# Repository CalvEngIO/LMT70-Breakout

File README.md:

# LMT70-Breakout
Breakout board for the LMT70/A CMOS analog temperature sensor from Texas Instruments

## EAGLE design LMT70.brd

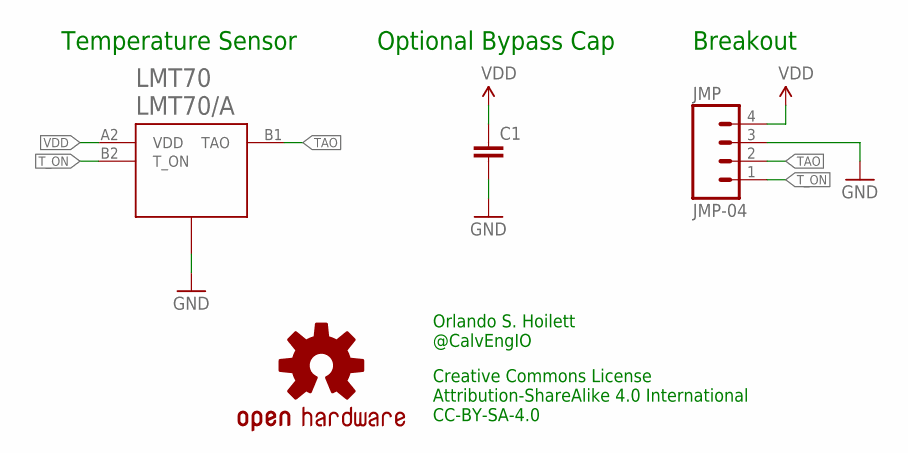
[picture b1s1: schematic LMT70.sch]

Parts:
C1: C-EUC0402; C0402
JMP: JMP-04
LMT70: LMT70/A; 4-DSBGA
LOGO1: OSHW-LOGOM; OSHW-LOGO-M

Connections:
GND: C1.2, JMP.3, LMT70.A1 (GND)
TAO: JMP.2, LMT70.B1 (TAO)
T_ON: JMP.1, LMT70.B2 (T_ON)
VDD: C1.1, JMP.4, LMT70.A2 (VDD)

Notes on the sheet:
Orlando S. Hoilett @CalvEngIO
Creative Commons License Attribution-ShareAlike 4.0 International CC-BY-SA-4.0
Temperature Sensor
Optional Bypass Cap
Breakout

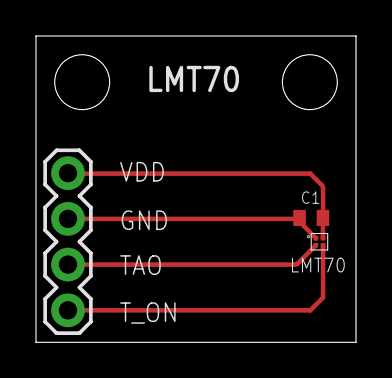
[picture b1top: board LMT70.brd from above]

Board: 2 copper layers, 17.8 x 17.0 mm, 4 parts (1 on the bottom side), 4 nets.

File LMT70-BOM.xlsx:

LMT70 Breakout |  |  |  |  |  |  |  |  |  |  | Total | 4.58
BOM # | Comment | Designator | Description | Mounting Type | Package | Manufacturer | Manufacturer Part Number | Supplier | Supplier Part Number | Quantity | Price per unit | Price Total
1 | LMT70A | LMT70 | Temperature Sensor Analog, Local -55°C ~ 150°C 5.194mV/°C 4-DSBGA (0.9x0.9) | SMD | 4-DSBGA (0.9x0.9) | Texas Insruments | LMT70AYFQT | Digi-Key | 296-42087-1-ND | 1 | 3.74 | 3.74
2 | 40 Pos Male Header Pins | JMP | 40 Positions Header, Breakaway Connector 0.100" (2.54mm) Through Hole Gold | THT | THT | Sullins Connector Solutions | PRPC040SAAN-RC | Digi-Key | S1011EC-40-ND | 1 | 0.74 | 0.74
3 | 0.10µF capacitor | C1 | 0.10µF ±10% 16V Ceramic Capacitor X7R 0402 (1005 Metric) | SMD | 0402 | Samsung Electro-Mechanics America, Inc. | CL05B104KO5NNNC | Digi-Key | 1276-1001-1-ND | 1 | 0.1 | 0.1

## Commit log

2017-02-10 Create LICENSE-hardware
2017-02-10 added PCB files
2017-03-03 GettingStarted skeleton. Needs writing

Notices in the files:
parts and their libraries:
SparkFun-Aesthetics: Licensing: Creative Commons ShareAlike 4.0 International - https://creativecommons.org/licenses/by-sa/4.0
